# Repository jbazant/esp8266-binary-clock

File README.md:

# WEMOS D1 mini Binary clock

This is a private project. No support is provided. No input expected. Also as soon as I finish 1st version, I will
probably not work on it anymore.

Esp8266 based, IKEA Skadis mounted, NTP synchronized, "smart" binary clock with temperature and humidity sensor.

Binary clock based on a WEMOS D1 mini and a 8x8 LED matrix. Shows the seconds, minutes, hours, day in month, day in
week, month, lunar phase and last two decimal digits of year in binary format.
Also uses a DHT sensor to show the temperature and humidity.
Time is synchronized via NTP.

Two buttons allow to disable display and set the brightness.

## How to read the clock

- Columns correspond to bits. Read them as (from right to left): 1, 2, 4, 8, 16, 32, 64.
- 8th bit is used for temperature as a sign bit (0 - positive, 1 - negative).
- Some rows have different meaning for top-most bits, but it should be obvious, once you get the idea.
- Labels on display cover should guide you.

### Rows

Rows from top to bottom:

- **1st row**: temperature (in Celsius) - 8th bit is a sign bit (0 - positive, 1 - negative)
- **2nd row**: relative humidity (in %) - 8th bit is not used (and it is also not visible on the display)
- **3rd row**: years - last two decimal digits (or year % 100, if you prefer), 8th bit is not used
  plate place is occupied by temperature labels)
- **4th row**:
    - Bits 1 - 4: months (1 = January, 12 = December)
    - Bits 5 - 8: lunar phase (see description below)
- **5th row**:
    - Bits 1 - 5: day in month
    - Bits 6 - 8: day of week - read from right to left - 6th bit means 1, 8th bit means 4 (1 = Monday, 7 = Sunday)
- **6th row**:
    - Bits 1 - 5: hours (24h format)
    - Bits 6 - 8: not used (and on the display plate place is occupied by day of week labels)
- **7th row**:
    - Bits 1 - 6: minutes
    - Bits 7 - 8: status bits for DHT sensor. 7 - last read failed (**E**rror), 8 - reading sensor in progress (**F**
      etching)
- **8th row**:
    - Bits 1 - 6: seconds
    - Bits 7 - 8: status bits for NTP synchronization. 7 - last synchronization failed (**E**rror), 8 - time
      synchronization in progress (**F**etching)

### Lunar phase

| Bits 5 - 8 | Lunar phase     | 🌝 |
|------------|-----------------|----|
| 0000       | New moon        | 🌑 |
| 0001       | Waxing crescent | 🌒 |
| 0011       | First quarter   | 🌓 |
| 0111       | Waxing gibbous  | 🌔 |
| 1111       | Full moon       | 🌕 |
| 1110       | Waning gibbous  | 🌖 |
| 1100       | Last quarter    | 🌗 |
| 1000       | Waning crescent | 🌘 |

Photo of the clock shows: Wednesday, 18th of September 2024, 12:17:35, full moon, 28°C, 52% relative humidity.

## Hardware

- WEMOS D1 mini
- 8x8 LED matrix with MAX7219 controller (FC-16)
- DHT22 sensor
- 2 buttons
- 4 pull-up 10kOhm resistors (2 for the buttons, 1 for the DHT sensor and 1 for reset pin)

## Software

The software is written as arduino project mostly in C++ and can be found in the `esp8266-binary-clock` folder (to
satisfy arduino project structure).

### Dependencies

- **DHT library** by Bert Melis ([GitHub](https://github.com/bertmelis/DHT))
- **NTP library** by Stefan Staub ([GitHub](https://github.com/sstaub/NTP))
- **LedController** library by Noah Kirschmann ([GitHub](https://github.com/noah1510/LedController))
- **moonPhaser** library by Cellie ([GitHub](https://github.com/CelliesProjects/moonPhase-esp32))
  - It claims to be not compatible with ESP8266, but it works just fine with version 2.0.0.
- **PubSubClient** (MQTT) by Nick O'Leary ([GitHub](https://github.com/knolleary/pubsubclient))

All dependencies are also listed in `esp8266-binary-clock/libraries.txt` for reference. Install them via Arduino IDE
(*Sketch > Include Library > Manage Libraries...*) or Arduino CLI (`arduino-cli lib install "<name>"`).

### Configuration

- Create `secrets.h` in the `esp8266-binary-clock` and specify your WiFi and MQTT credentials. (see `secrets-example.h`)
- Adjust `CONFIGURATION` section and `initTimezoneAndDST` method in `esp8266-binary-clock.ino` to your needs (or just
  leave as is).
    - `DHT_INTERVAL_S` - interval for reading DHT sensor (in seconds), default 1 minute
    - `NTP_INTERVAL_S` - interval for NTP synchronization (in seconds), default 12 hours
    - `MQTT_PUBLISH_INTERVAL_S` - interval for publishing temperature & humidity via MQTT (in seconds), default 10 minutes

## Home Assistant

See [`docs/home-assistant.md`](docs/home-assistant.md) for MQTT sensor configuration, an automation example, and a Lovelace card snippet.

## PCB

The PCB is designed in KiCad and can be found in the `pcb` folder. Size of the PCB board is 66 x58 mm with LED matrix
and DHT22 sensor overhanging the board.
Board is actually pretty simple and uses just one Cu layer and 0.5mm clearance between tracks. You need to use 1.6mm PCB
thickness or adjust the case (bottom part).

## Case

The case is designed in OpenScad and can be found in the `case` folder. Optimized (well as much as I was able to...) for
FDM 3D printing.

- optimized for 0.4mm nozzle and 0.2mm layer height
- tested with PLA
- no supports
- 2 perimeters and 15% infill is more than enough

Case is divided into 3 parts:

- bottom (`case_bottom.scad`)
- top (`case_top.scad`)
- display cover (`display_plate.scad`)

One can render all parts with the `case.scad` file.

All the parts should snap together without any screws or glue.

### Dependencies

- **BOSL library** by Revar Desmera ([GitHub](https://github.com/revarbat/BOSL)).
- **Roboto** (bold) font by Christian Robertson ([Google fonts](https://fonts.google.com/specimen/Roboto0)).

### Case bottom

Case is printed with supports that are included in the model. Do not add supports in slicer! After printing, remove
the "triangle" simply by tilting it back and forth
and "mouse ears" with a knife.

Assembled PCB (optimized for 1.6mm height) should fit into the model without any screws or glue. Some force is needed to
snap it in.

### Case top

- *(Optional)* color change at heights:
    - Start with color for "ventilation" grids.
    - Change color at 1.4mm for the base one.

### Display cover

- Use some pretty contrast colors for the display cover. Change filament color at the height of 1.2mm.
- *(Optional)* Use nozzle of 0.25mm for better readability of the labels.

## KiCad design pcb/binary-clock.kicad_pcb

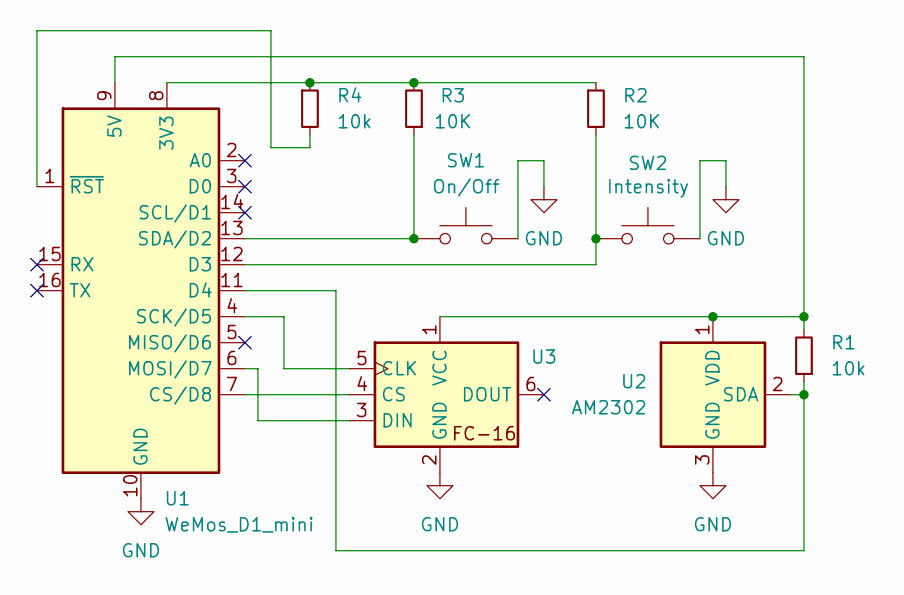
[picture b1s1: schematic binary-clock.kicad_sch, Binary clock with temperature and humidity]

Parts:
R1, R4: 10k; R_Axial_DIN0207_L6.3mm_D2.5mm_P10.16mm_Horizontal
R2, R3: 10K; R_Axial_DIN0207_L6.3mm_D2.5mm_P10.16mm_Horizontal
SW1: On/Off; SW_PUSH-12mm
SW2: Intensity; SW_PUSH-12mm
U1: WeMos_D1_mini; WEMOS_D1_mini_light
U2: AM2302; ASAIR_AM2302_P2.54mm_Lead2.75mm_TabDown
U3: FC-16

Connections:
GND: SW1.2, SW2.2, U1.10 (GND), U2.3 (GND), U2.4 (GND), U3.2 (GND)
unnamed: R2.1, R3.2, R4.1, U1.8 (3V3)
unnamed: R1.2, U1.9 (5V), U2.1 (VDD), U3.1 (VCC)
unnamed: U1.7 (CS/D8), U3.4 (CS)
unnamed: R2.2, SW2.1, U1.12 (D3)
unnamed: R1.1, U1.11 (D4), U2.2 (SDA)
unnamed: U1.6 (MOSI/D7), U3.3 (DIN)
unnamed: U1.4 (SCK/D5), U3.5 (CLK)
unnamed: R3.1, SW1.1, U1.13 (SDA/D2)
unnamed: R4.2, U1.1 (~RST)

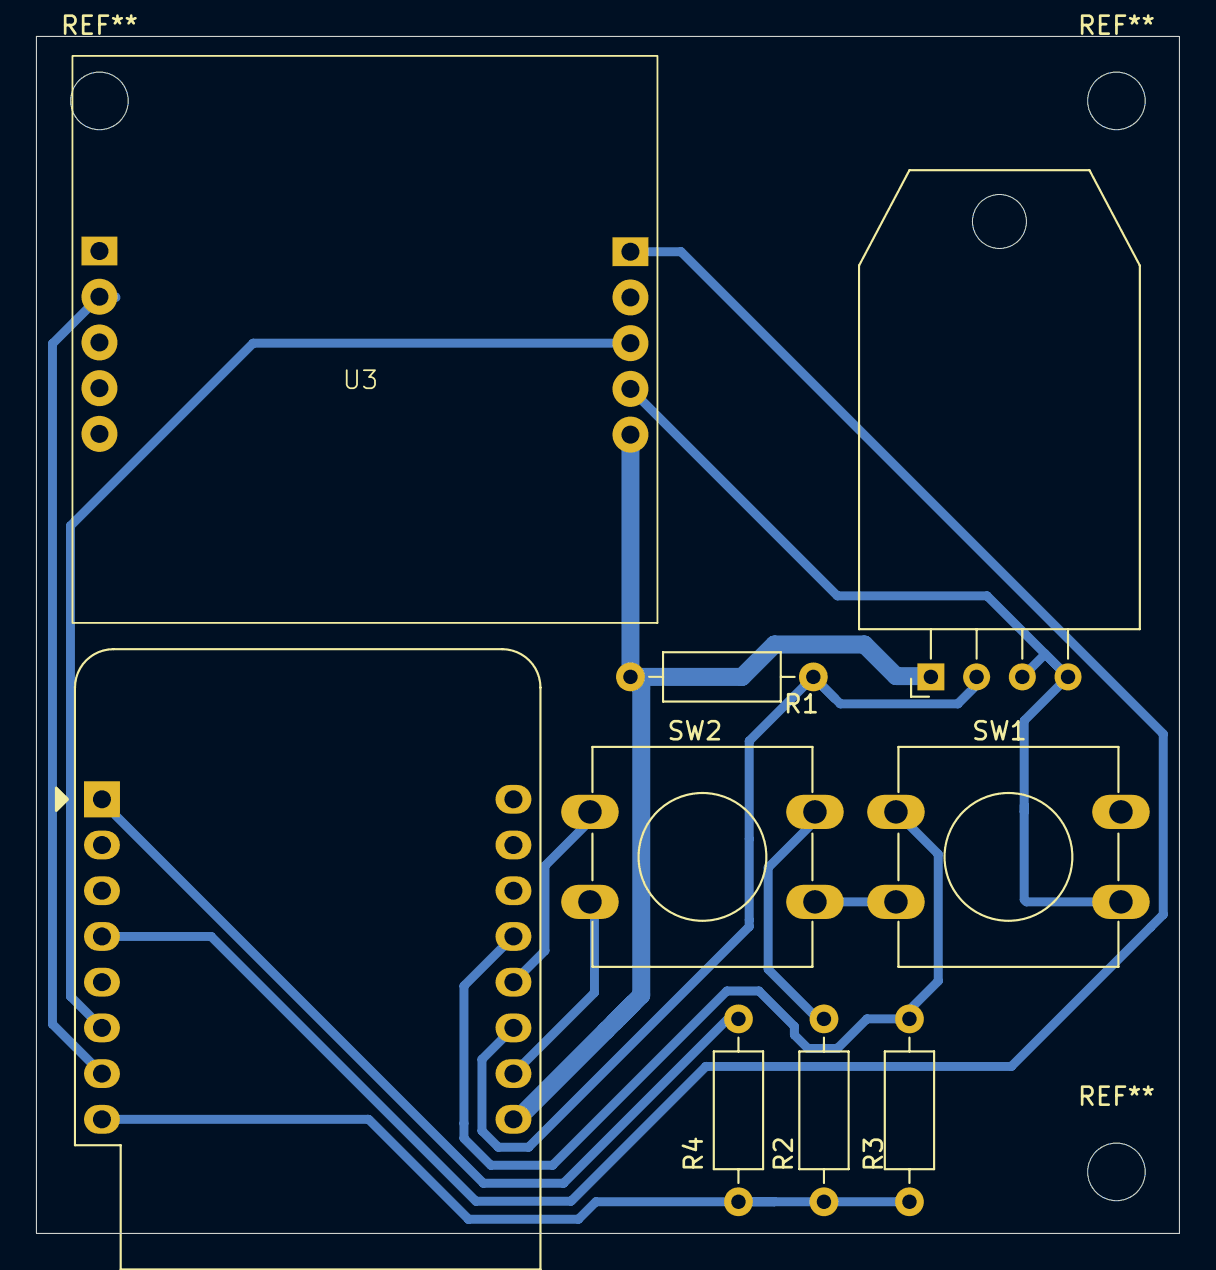
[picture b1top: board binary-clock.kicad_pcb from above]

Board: 2 copper layers, 63.5 x 66.5 mm, 9 parts (0 on the bottom side), 10 nets.

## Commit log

2024-08-29 secrets example file
2024-08-29 move wifi configuration to MyNTPClient constructor arguments
2024-08-29 minor design changes
2024-08-29 fix button mismatch
2024-08-30 Improve MyNTPClient error handling, refactoring
2024-08-30 WIP: case OpenScad model - display plate first candidate
2024-08-30 Show WIFI error on display
2024-09-02 Show moon phase next to month
2024-09-02 Readme update
2024-09-05 .gitignore update
2024-09-05 PCB prototype in KiCad
2024-09-05 fix: Fix crash on NTP sync by introducing own Ticker implementation
2024-09-05 chore: remove author comment from MyNTPClient.h
2024-09-05 feat: Introduce TickerController
2024-09-05 feat: introduce REFRESH_RATE_MS
2024-09-05 chore: refactor ClockDisplay intensity by introducing DEFAULT_INTENSITY and INTENSITY_STEP
2024-09-12 feat: new pcb layout
2024-09-16 feat: case - basic version
2024-09-16 feat: use DHT22 instead of DHT11
2024-09-16 chore: better and separate .3mf files
2024-09-17 chore: adjust constants in arduino code
2024-09-17 chore: improve docs
2024-09-18 chore: adjust lock tolerances
2024-09-18 chore: added photo to readme
2026-04-19 feat: use static IP and fast connect
2026-04-19 feat: use MQTT for reporting temperature and humidity
2026-04-19 chore: Update usage of MoonPhase to v2.0.0
2026-04-19 chore: Update HA docs
2026-04-22 feat: implement state machine for MyMQTT to handle WiFi and MQTT connection flow
2026-04-22 feat: add configurable temperature and humidity offsets in DHT sensor and improve float precision handling
2026-04-22 chore: adjust DHT temperature offset
2026-04-22 chore: switch DHT temperature and humidity calculations to use round instead of trunc
